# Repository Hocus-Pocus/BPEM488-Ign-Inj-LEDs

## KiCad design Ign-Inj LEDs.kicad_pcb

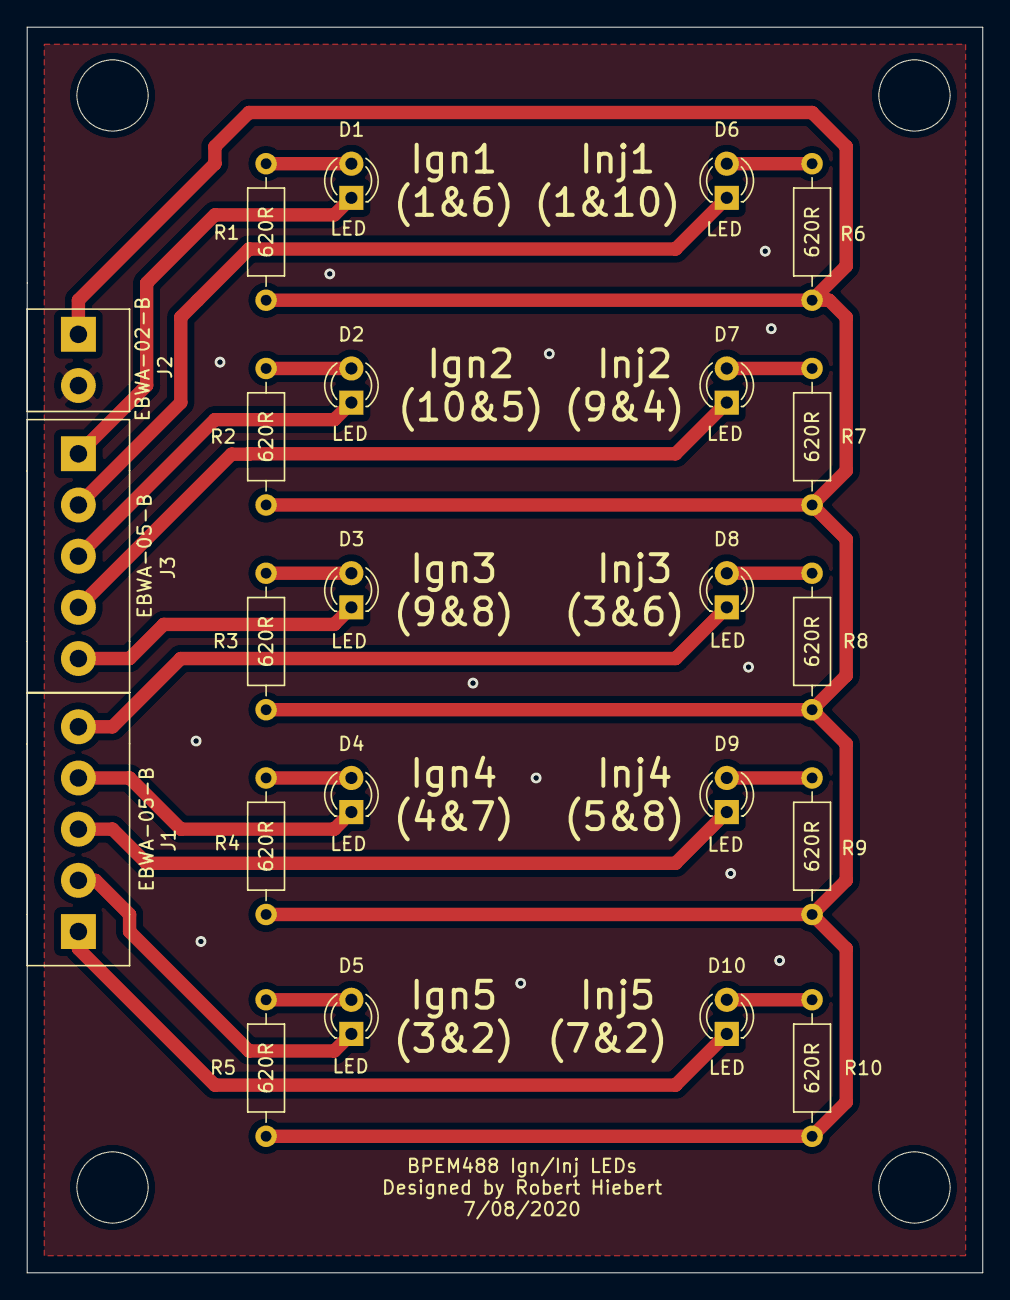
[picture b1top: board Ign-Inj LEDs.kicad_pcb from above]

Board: 2 copper layers, 71.1 x 92.7 mm, 23 parts (0 on the bottom side), 21 nets.

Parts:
D1, D2, D3, D4, D5, D6, D7, D8, D9, D10: LED; LED_D3.0mm
J1, J3: EBWA-05-B
J2: EBWA-02-B
R1, R2, R3, R4, R5, R6, R7, R8, R9, R10: 620R; R_Axial_DIN0207_L6.3mm_D2.5mm_P10.16mm_Horizontal

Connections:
+12V: J2.1, R1.1, R2.1, R3.1, R4.1, R5.1, R6.2, R7.2, R8.2, R9.2, R10.2
/Inj1: D6.1, J3.2
/Inj2: D7.1, J3.4
/Inj3: D8.1, J1.5
/Inj4: D9.1, J1.3
/Inj5: D10.1, J1.1
unnamed: D1.1, J3.1
unnamed: D1.2, R1.2
unnamed: D2.1, J3.3
unnamed: D2.2, R2.2
unnamed: D3.1, J3.5
unnamed: D3.2, R3.2
unnamed: D4.1, J1.4
unnamed: D4.2, R4.2
unnamed: D5.1, J1.2
unnamed: D5.2, R5.2
unnamed: D6.2, R6.1
unnamed: D7.2, R7.1
unnamed: D8.2, R8.1
unnamed: D9.2, R9.1
unnamed: D10.2, R10.1
